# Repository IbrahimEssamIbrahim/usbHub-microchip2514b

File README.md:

# usbHub-microchip2514b
A while ago, I purchased a new laptop with impressive performance capabilities. However, I encountered an issue with the limited number of ports it supported. As a result, I began searching for a high-quality USB hub, also known as a dongle. During my search, I became a bit curious about how these devices operate, their internal components, and, most importantly, what it would entail to design one myself.
 
After doing some research, I stumbled upon the USB251xB chips, which belong to the USB 2.0 Hi-Speed (480Mbps) hub controller family manufactured by Microchip Technology. These hub controllers are specifically designed to offer USB connectivity and hub functionality to a wide range of electronic devices, including laptops, desktop computers, embedded systems, and more. They are available in various configurations, each offering a different number of downstream USB ports. The 'x' in USB251xB denotes the specific number of ports available in a particular variant (e.g., USB2512B has 2 ports, USB2514B has 4 ports).
 
I found the USB2514B to be the most suitable chip for my design, as it provides an adequate number of ports for my needs. As a starting point for PCB layout, I referred to the designs and application notes provided in the datasheet. I’ve tried as much as possible to follow recommended component placement, power and ground plans, and routing considerations, particularly for the differential pairs associated with USB data lines (D+ and D-). This was done to maintain consistent trace lengths and minimize skew.
 
Additionally, I came across several videos on the Phil’s Lab YouTube channel, which proved me with very helpful information to refining my final design.
 
Here are the specifications of the product:
* connects to the host via a micro-USB-B 2.0 port and provides 4 USB ports.
* Includes USB protection to safeguard against static discharges.
* Can supply up to 500mA of current to connected devices.
* Supports an external 5V-DC power jack for added versatility.
 
 Once I was satisfied with the PCB design, I created a case for the USB hub with fusion 360 that could be 3D printed.

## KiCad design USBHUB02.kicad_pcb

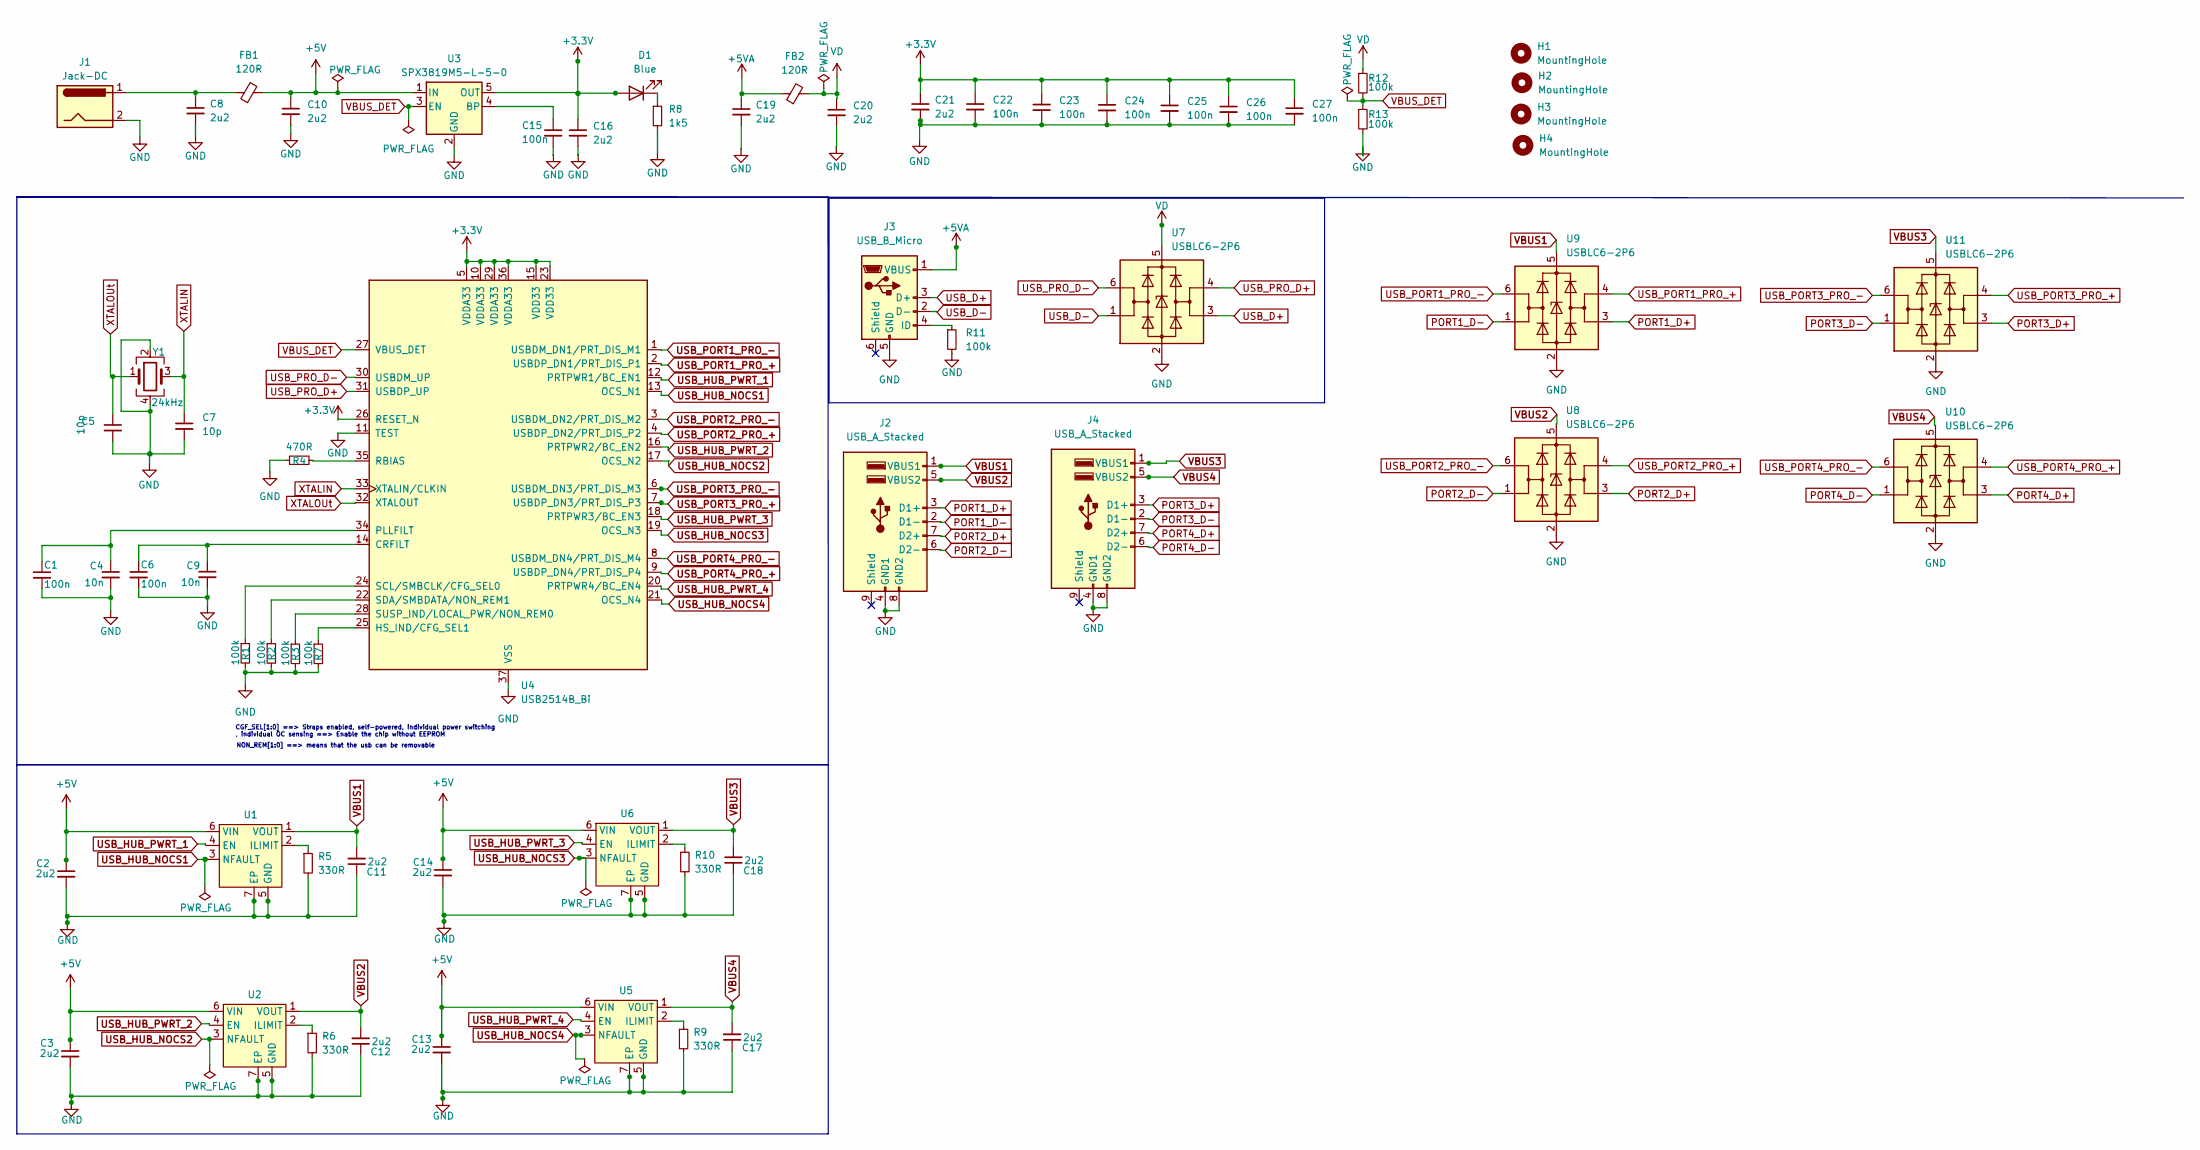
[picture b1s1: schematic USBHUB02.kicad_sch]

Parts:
C1, C6, C22, C23, C24, C25, C26, C27: 100n; C_0402_1005Metric_Pad0.74x0.62mm_HandSolder
C2, C3, C11, C12, C13, C14, C17, C18: 2u2; C_0603_1608Metric
C4, C9: 10n; C_0402_1005Metric_Pad0.74x0.62mm_HandSolder
C5, C7: 10p; C_0402_1005Metric_Pad0.74x0.62mm_HandSolder
C8, C10, C16, C19, C20: 2u2; C_0805_2012Metric
C15: 100n; C_0805_2012Metric
C21: 2u2; C_0402_1005Metric_Pad0.74x0.62mm_HandSolder
D1: Blue; LED_0603_1608Metric
FB1, FB2: 120R; L_1206_3216Metric
H1, H2, H3, H4: MountingHole; MountingHole_2.1mm
J1: Jack-DC; BarrelJack_Horizontal
J2, J4: USB_A_Stacked; USB_A_CUI_UJ2-ADH-TH_Horizontal_Stacked
J3: USB_B_Micro; USB_Micro-B_Molex-105017-0001
R1, R2, R3, R7, R11, R12, R13: 100k; R_0603_1608Metric
R4: 470R; R_0402_1005Metric
R5, R6, R9, R10: 330R; R_0402_1005Metric
R8: 1k5; R_0402_1005Metric_Pad0.72x0.64mm_HandSolder
U1, U2, U5, U6: SON50P160X160X60-7N
U3: SPX3819M5-L-5-0; SOT-23-5
U4: USB2514B_Bi; QFN-36-1EP_6x6mm_P0.5mm_EP3.7x3.7mm
U7, U8, U9, U10, U11: USBLC6-2P6; SOT-666
Y1: 24kHz; Crystal_SMD_3225-4Pin_3.2x2.5mm

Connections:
+3.3V: C16.1, C21.1, C22.1, C23.1, C24.1, C25.1, C26.1, C27.1, D1.2 (A), U3.5 (OUT), U4.5 (VDDA33), U4.10 (VDDA33), U4.15 (VDD33), U4.23 (VDD33), U4.26 (RESET_N), U4.29 (VDDA33), U4.36 (VDDA33)
+5V: C2.1, C3.1, C10.1, C13.1, C14.1, FB1.2, U1.6 (VIN), U2.6 (VIN), U3.1 (IN), U5.6 (VIN), U6.6 (VIN)
+5VA: C19.1, FB2.1, J3.1 (VBUS)
GND: C1.2, C2.2, C3.2, C4.2, C5.2, C6.2, C7.2, C8.2, C9.2, C10.2, C11.1, C12.1, C13.2, C14.2, C15.2, C16.2, C17.1, C18.1, C19.2, C20.2, C21.2, C22.2, C23.2, C24.2, C25.2, C26.2, C27.2, J1.2, J2.4 (GND1), J2.8 (GND2), J3.5 (GND), J4.4 (GND1), J4.8 (GND2), R1.2, R2.2, R3.2, R4.1, R5.2, R6.2, R7.2, R8.2, R9.2, R10.2, R11.2, R13.2, U1.5 (GND), U1.7 (EP), U2.5 (GND), U2.7 (EP), U3.2 (GND), U4.11 (TEST), U4.37 (VSS), U5.5 (GND), U5.7 (EP), U6.5 (GND), U6.7 (EP), U7.2 (GND), U8.2 (GND), U9.2 (GND), U10.2 (GND), U11.2 (GND), Y1.2, Y1.4
unnamed: C8.1, FB1.1, J1.1
unnamed: D1.1 (K), R8.1
unnamed: J3.4 (ID), R11.1
unnamed: R12.2, R13.1
unnamed: R5.1, U1.2 (ILIMIT)
unnamed: R6.1, U2.2 (ILIMIT)
unnamed: C15.1, U3.4 (BP)
unnamed: C6.1, C9.1, U4.14 (CRFILT)
unnamed: R7.1, U4.25 (HS_IND/CFG_SEL1)
unnamed: C1.1, C4.1, U4.34 (PLLFILT)
unnamed: R4.2, U4.35 (RBIAS)
unnamed: R1.1, U4.24 (SCL/SMBCLK/CFG_SEL0)
unnamed: R2.1, U4.22 (SDA/SMBDATA/NON_REM1)
unnamed: R3.1, U4.28 (SUSP_IND/LOCAL_PWR/NON_REM0)
unnamed: R9.1, U5.2 (ILIMIT)
unnamed: R10.1, U6.2 (ILIMIT)
PORT1_D+: J2.3 (D1+), U9.3 (I/O2)
PORT1_D-: J2.2 (D1-), U9.1 (I/O1)
PORT2_D+: J2.7 (D2+), U8.3 (I/O2)
PORT2_D-: J2.6 (D2-), U8.1 (I/O1)
PORT3_D+: J4.3 (D1+), U11.3 (I/O2)
PORT3_D-: J4.2 (D1-), U11.1 (I/O1)
PORT4_D+: J4.7 (D2+), U10.3 (I/O2)
PORT4_D-: J4.6 (D2-), U10.1 (I/O1)
USB_D+: J3.3 (D+), U7.3 (I/O2)
USB_D-: J3.2 (D-), U7.1 (I/O1)
USB_HUB_NOCS1: U1.3 (NFAULT), U4.13 (OCS_N1)
USB_HUB_NOCS2: U2.3 (NFAULT), U4.17 (OCS_N2)
USB_HUB_NOCS3: U4.19 (OCS_N3), U6.3 (NFAULT)
USB_HUB_NOCS4: U4.21 (OCS_N4), U5.3 (NFAULT)
USB_HUB_PWRT_1: U1.4 (EN), U4.12 (PRTPWR1/BC_EN1)
USB_HUB_PWRT_2: U2.4 (EN), U4.16 (PRTPWR2/BC_EN2)
USB_HUB_PWRT_3: U4.18 (PRTPWR3/BC_EN3), U6.4 (EN)
USB_HUB_PWRT_4: U4.20 (PRTPWR4/BC_EN4), U5.4 (EN)
USB_PORT1_PRO_+: U4.2 (USBDP_DN1/PRT_DIS_P1), U9.4 (I/O2)
USB_PORT1_PRO_-: U4.1 (USBDM_DN1/PRT_DIS_M1), U9.6 (I/O1)
USB_PORT2_PRO_+: U4.4 (USBDP_DN2/PRT_DIS_P2), U8.4 (I/O2)
USB_PORT2_PRO_-: U4.3 (USBDM_DN2/PRT_DIS_M2), U8.6 (I/O1)
USB_PORT3_PRO_+: U4.7 (USBDP_DN3/PRT_DIS_P3), U11.4 (I/O2)
USB_PORT3_PRO_-: U4.6 (USBDM_DN3/PRT_DIS_M3), U11.6 (I/O1)
USB_PORT4_PRO_+: U4.9 (USBDP_DN4/PRT_DIS_P4), U10.4 (I/O2)
USB_PORT4_PRO_-: U4.8 (USBDM_DN4/PRT_DIS_M4), U10.6 (I/O1)
USB_PRO_D+: U4.31 (USBDP_UP), U7.4 (I/O2)
USB_PRO_D-: U4.30 (USBDM_UP), U7.6 (I/O1)
VBUS1: C11.2, J2.1 (VBUS1), U1.1 (VOUT), U9.5 (VBUS)
VBUS2: C12.2, J2.5 (VBUS2), U2.1 (VOUT), U8.5 (VBUS)
VBUS3: C18.2, J4.1 (VBUS1), U6.1 (VOUT), U11.5 (VBUS)
VBUS4: C17.2, J4.5 (VBUS2), U5.1 (VOUT), U10.5 (VBUS)
VBUS_DET: U3.3 (EN), U4.27 (VBUS_DET)
VD: C20.1, FB2.2, R12.1, U7.5 (VBUS)
XTALIN: C7.1, U4.33 (XTALIN/CLKIN), Y1.3
XTALOUt: C5.1, U4.32 (XTALOUT), Y1.1

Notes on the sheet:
CGF_SEL[1:0] ==> Straps enabled, self-powered, individual power switching , individual OC sensing ==> Enable the chip without EEPROM
NON_REM[1:0] ==> means that the usb can be removable

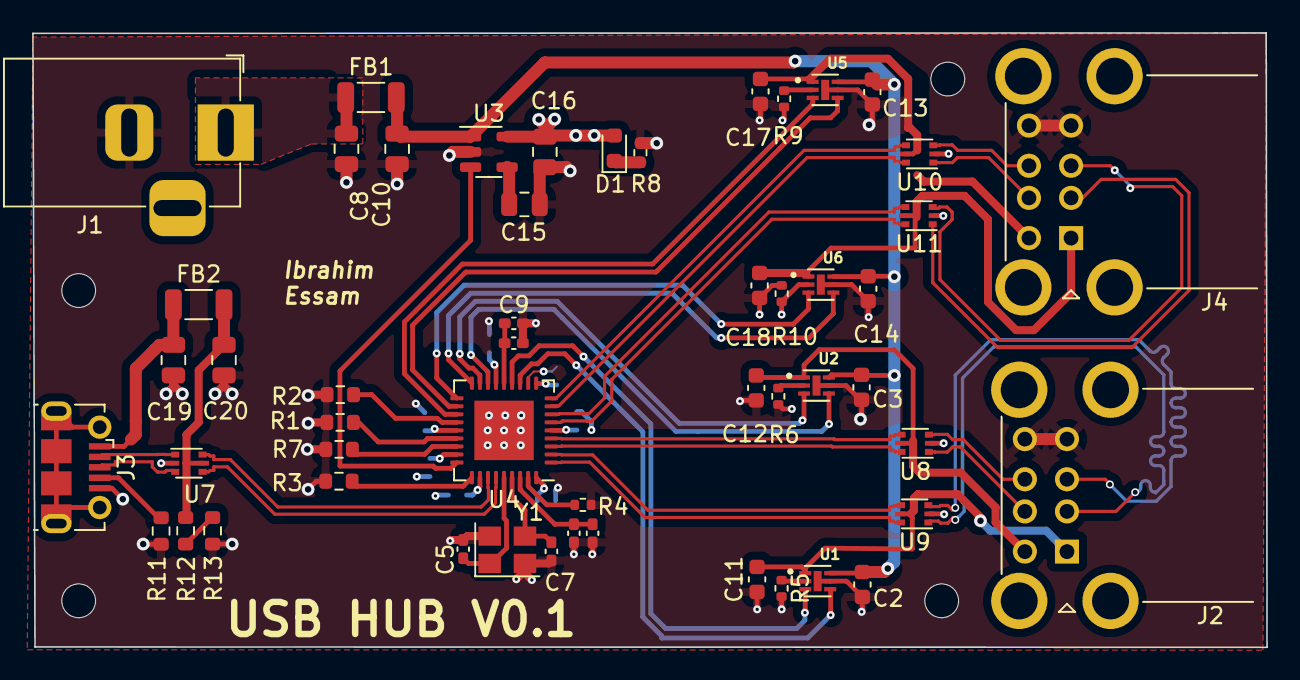
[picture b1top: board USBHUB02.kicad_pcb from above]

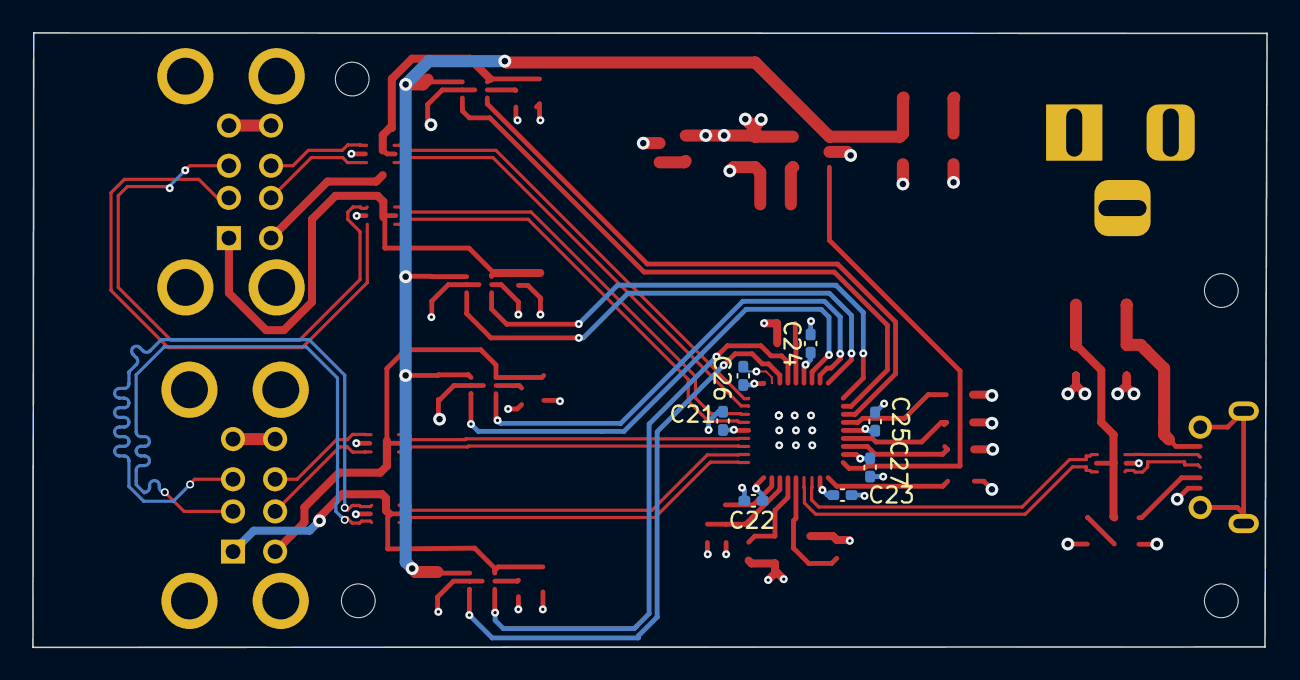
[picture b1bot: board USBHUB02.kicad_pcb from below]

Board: 4 copper layers, 76.8 x 38.2 mm, 63 parts (7 on the bottom side), 56 nets.
